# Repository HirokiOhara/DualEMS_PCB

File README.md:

# EiMS_PCB

This repository contains source code of software from our work "DualEMS: Two-Channel Arbitrary Waveform Electrical Muscle Stimulation Device to Design Interference Stimulation" (ACM AHs2022).

## Hardware Implimentation

## Authors
Hiroki Ohara, Tokyo Tech ( h.ohara[at]gs.haselab.net )

## Citation
When using or building upon this device/work in an academic publication, please consider citing as follows:
```
Hiroki Ohara and Shoichi Hasegawa. 2022. DualEMS: Two-Channel Arbitrary Waveform Electrical Muscle Stimulation Device to Design Interference Stimulation. In Augmented Humans 2022 (AHs 2022), March 13–15, 2022, Kashiwa, Chiba, Japan. ACM, New York, NY, USA, 8 pages. https://doi.org/10.1145/3519391.3519415
```

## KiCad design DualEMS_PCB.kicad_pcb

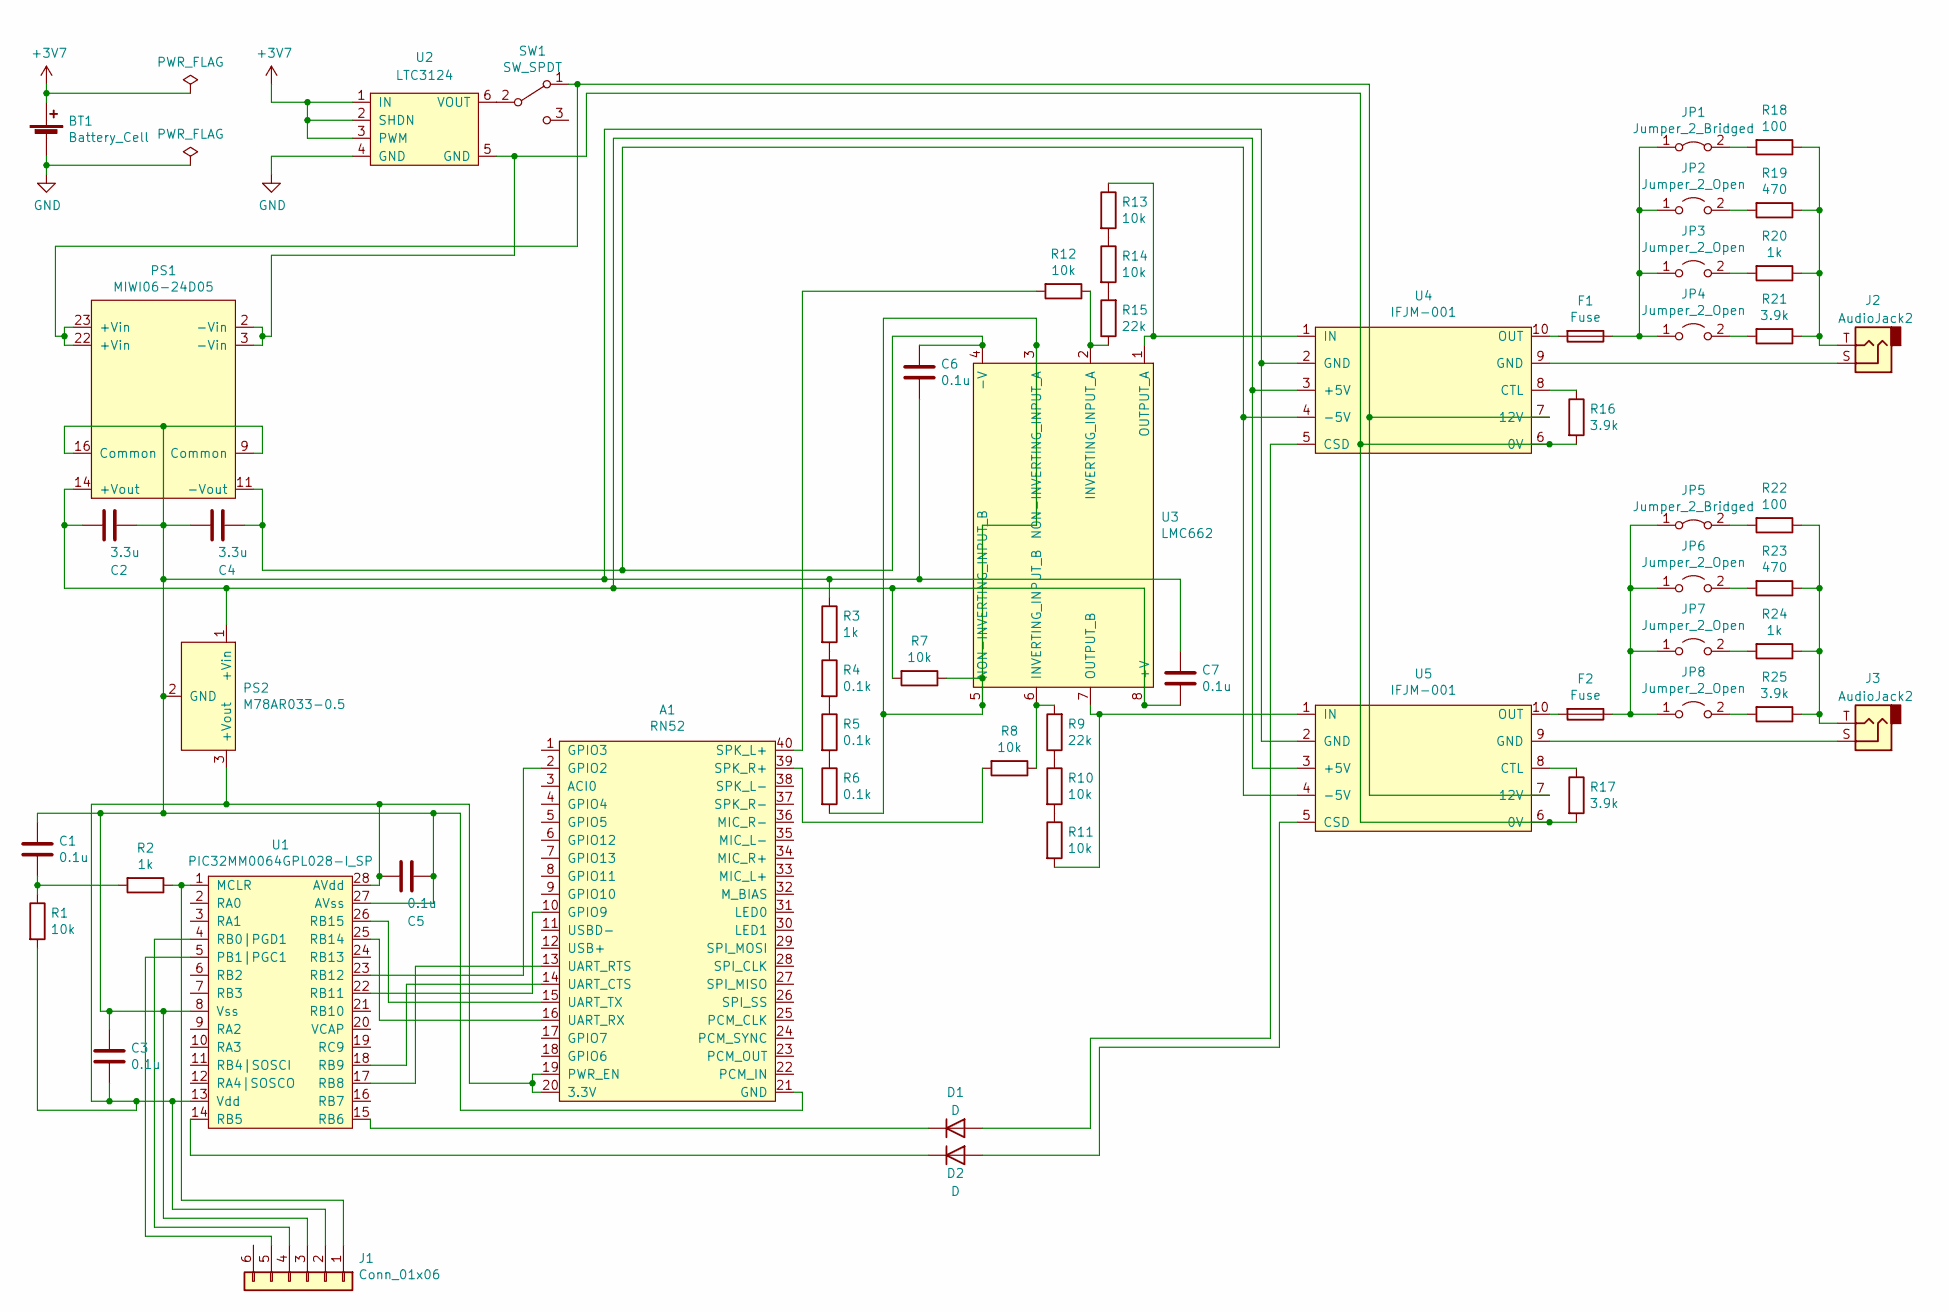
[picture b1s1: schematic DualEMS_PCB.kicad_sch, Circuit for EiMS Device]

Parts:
A1: RN52
BT1: Battery_Cell; Battery_+3V7
C1, C3, C5, C6, C7: 0.1u; C_Radial_P5.00mm
C2, C4: 3.3u; C_Radial_P5.00mm
D1, D2: D; D_A-405_P10.16mm_Horizontal
F1, F2: Fuse; FUC-04
J1: Conn_01x06; PinHeader_1x06_P2.54mm_Horizontal
J2, J3: AudioJack2; MJ-352
JP1, JP5: Jumper_2_Bridged; PinHeader_1x02_P2.54mm_Vertical
JP2, JP3, JP4, JP6, JP7, JP8: Jumper_2_Open; PinHeader_1x02_P2.54mm_Vertical
PS1: MIWI06-24D05
PS2: M78AR033-0.5
R1, R7, R8, R10, R11, R12, R13, R14: 10k; R_Axial_DIN0207_L6.3mm_D2.5mm_P7.62mm_Horizontal
R2, R3, R20, R24: 1k; R_Axial_DIN0207_L6.3mm_D2.5mm_P7.62mm_Horizontal
R4, R5, R6: 0.1k; R_Axial_DIN0207_L6.3mm_D2.5mm_P7.62mm_Horizontal
R9, R15: 22k; R_Axial_DIN0204_L3.6mm_D1.6mm_P5.08mm_Horizontal
R16, R17, R21, R25: 3.9k; R_Axial_DIN0207_L6.3mm_D2.5mm_P7.62mm_Horizontal
R18, R22: 100; R_Axial_DIN0207_L6.3mm_D2.5mm_P7.62mm_Horizontal
R19, R23: 470; R_Axial_DIN0207_L6.3mm_D2.5mm_P7.62mm_Horizontal
SW1: SW_SPDT; MS-500A-MF-K
U1: PIC32MM0064GPL028-I_SP
U2: LTC3124
U3: LMC662
U4, U5: IFJM-001

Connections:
+3V7: BT1.1 (+), U2.1 (IN), U2.2 (SHDN), U2.3 (PWM)
GND: BT1.2 (-), U2.4 (GND)
unnamed: A1.2 (GPIO2), U1.23 (RB12)
unnamed: A1.10 (GPIO9), U1.22 (RB11)
unnamed: A1.13 (UART_RTS), U1.17 (RB8)
unnamed: A1.14 (UART_CTS), U1.18 (RB9)
unnamed: A1.15 (UART_TX), U1.26 (RB15)
unnamed: A1.16 (UART_RX), U1.25 (RB14)
unnamed: A1.19 (PWR_EN), A1.20 (3.3V), C3.2, C5.1, J1.2, PS2.3 (+Vout), R1.2, U1.13 (Vdd), U1.28 (AVdd)
unnamed: A1.21 (GND), C1.1, C2.2, C3.1, C4.1, C5.2, C6.1, C7.2, J1.3, PS1.9 (Common), PS1.16 (Common), PS2.2 (GND), R3.1, U1.8 (Vss), U1.27 (AVss), U4.2 (GND), U5.2 (GND)
unnamed: A1.39 (SPK_R+), R8.2
unnamed: A1.40 (SPK_L+), R12.2
unnamed: C1.2, R1.1, R2.2
unnamed: C2.1, C7.1, PS1.14 (+Vout), PS2.1 (+Vin), R7.2, U3.8 (+V), U4.3 (+5V), U5.3 (+5V)
unnamed: C4.2, C6.2, PS1.11 (-Vout), U3.4 (-V), U4.4 (-5V), U5.4 (-5V)
unnamed: D1.1 (K), U1.15 (RB6)
unnamed: D1.2 (A), U4.5 (CSD)
unnamed: D2.1 (K), U1.14 (RB5)
unnamed: D2.2 (A), U5.5 (CSD)
unnamed: F1.1, JP1.1 (A), JP2.1 (A), JP3.1 (A), JP4.1 (A)
unnamed: F1.2, U4.10 (OUT)
unnamed: F2.1, JP5.1 (A), JP6.1 (A), JP7.1 (A), JP8.1 (A)
unnamed: F2.2, U5.10 (OUT)
unnamed: J1.1, R2.1, U1.1 (MCLR)
unnamed: J1.4, U1.4 (RB0|PGD1)
unnamed: J1.5, U1.5 (PB1|PGC1)
unnamed: J2.S, U4.9 (GND)
unnamed: J2.T, R18.1, R19.1, R20.1, R21.1
unnamed: J3.S, U5.9 (GND)
unnamed: J3.T, R22.1, R23.1, R24.1, R25.1
unnamed: JP1.2 (B), R18.2
unnamed: JP2.2 (B), R19.2
unnamed: JP3.2 (B), R20.2
unnamed: JP4.2 (B), R21.2
unnamed: JP5.2 (B), R22.2
unnamed: JP6.2 (B), R23.2
unnamed: JP7.2 (B), R24.2
unnamed: JP8.2 (B), R25.2
unnamed: PS1.2 (-Vin), PS1.3 (-Vin), R16.2, R17.2, U2.5 (GND), U4.6 (0V), U5.6 (0V)
unnamed: PS1.22 (+Vin), PS1.23 (+Vin), SW1.1 (A), U4.7 (12V), U5.7 (12V)
unnamed: R3.2, R4.1
unnamed: R4.2, R5.1
unnamed: R5.2, R6.1
unnamed: R6.2, R7.1, U3.3 (NON-INVERTING_INPUT_A), U3.5 (NON-INVERTING_INPUT_B)
unnamed: R8.1, R9.2, U3.6 (INVERTING_INPUT_B)
unnamed: R9.1, R10.1
unnamed: R10.2, R11.1
unnamed: R11.2, U3.7 (OUTPUT_B), U5.1 (IN)
unnamed: R12.1, R15.1, U3.2 (INVERTING_INPUT_A)
unnamed: R13.1, U3.1 (OUTPUT_A), U4.1 (IN)
unnamed: R13.2, R14.1
unnamed: R14.2, R15.2
unnamed: R16.1, U4.8 (CTL)
unnamed: R17.1, U5.8 (CTL)
unnamed: SW1.2 (B), U2.6 (VOUT)

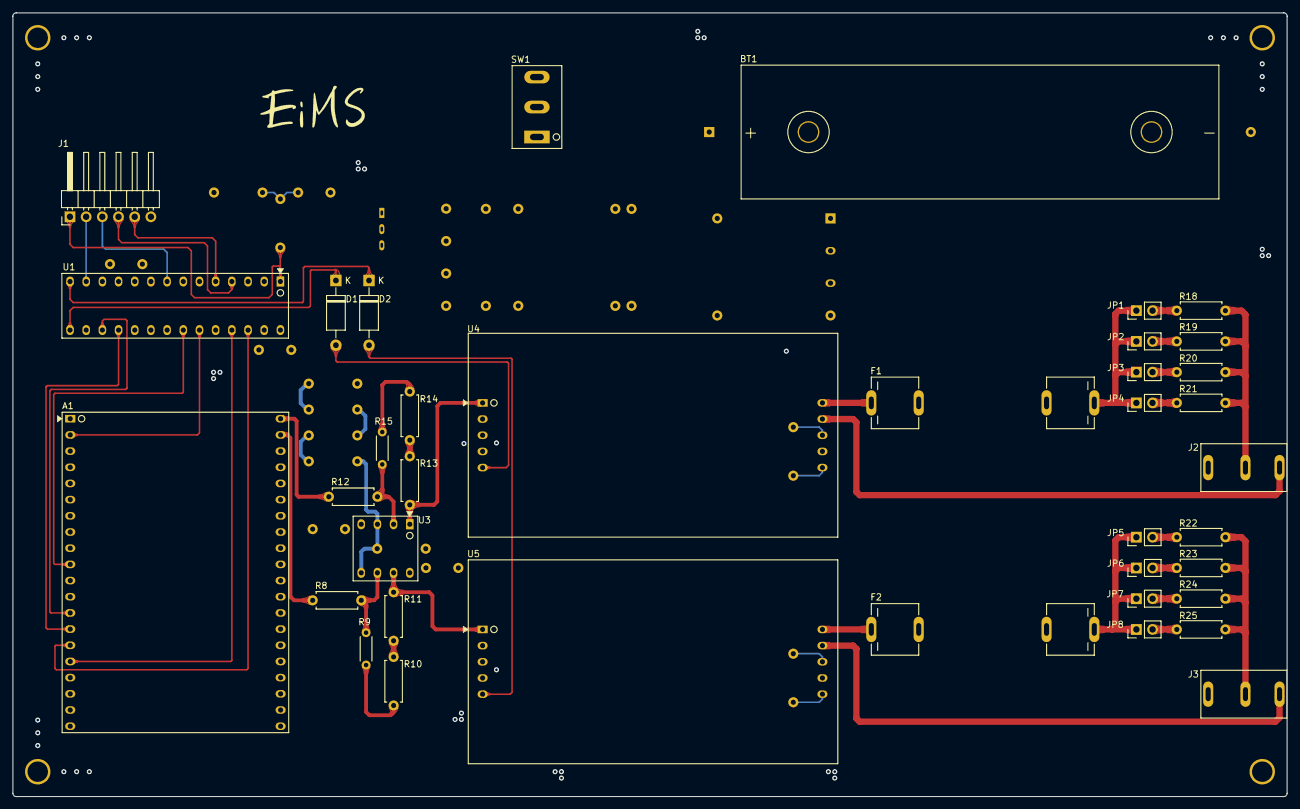
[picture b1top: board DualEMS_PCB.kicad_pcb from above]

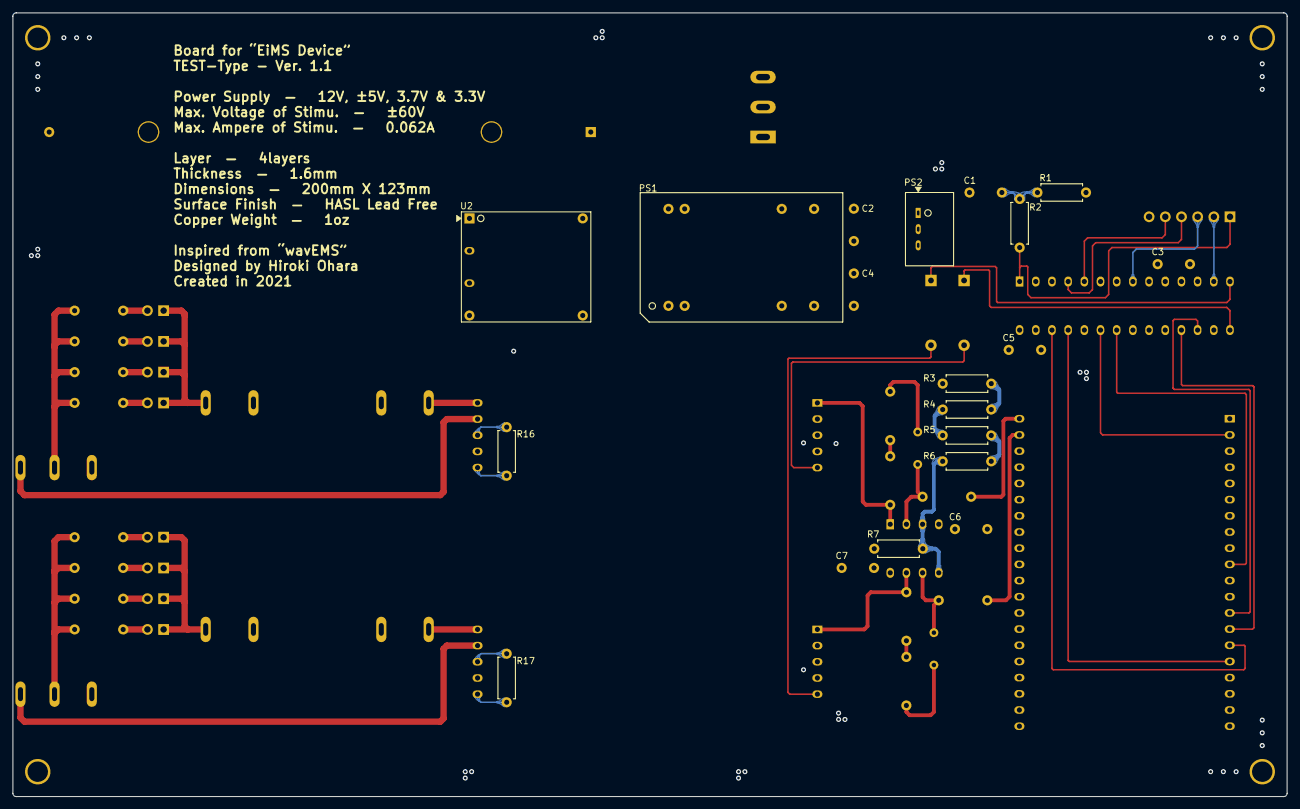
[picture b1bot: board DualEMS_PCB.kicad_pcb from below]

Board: 4 copper layers, 200.0 x 123.0 mm, 61 parts (19 on the bottom side), 55 nets.

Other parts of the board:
REF1, REF2, REF3, REF4: MountingHole_3.2mm_M3_Pad

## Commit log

2022-01-26 final
2022-03-08 changed name
2022-03-08 updated for kiCad 6.0
